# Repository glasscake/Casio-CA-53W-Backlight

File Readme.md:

# Casio-CA-53W Backlight Modification PCB

## Description
This is a PCB that adds backlight functonality to Casio-CA-53W style watches. It could potentially work with other Casio watches as well.

This project is still very green, a rev A board has been produced and is being tested. significant redesigns are still needed to improve preformance and relability in assembly.
Watch the project and see how development goes.

The design files are made in [KiCad](https://www.kicad.org/) an open source PCB design software.

## Make Your Own
Rev A boards have been produced from JLCPCB; uploading [Rev A.zip](Gerber%20Files/Rev%20A/Rev%20A.zip) to JLCPCB's or other PCB manufacturer's online portal and selecting flex PCB with ENIG sohuld get you boards similar to my own.  
Once a suitable design has been found more thorough ordering instructions will be provided. The current design also has a stiffener, this has no benifit and is not required.

Current limiting resistors can be ommited if diodes with a foward voltage close to 3.0v are carefuly chosen. I am using [Vishay VLMW15 serires](https://www.digikey.com/en/products/detail/vishay-semiconductor-opto-division/VLMW1500-GS08/3504672) 0402(imperial) LEDs at the moment.  
These LEDs have a typical forward voltage of 2.9 volts which means when using the Casio's 3.0v battery the foward current is around 5mA very well within the 20mA rating of the componets. So shunts or solder bridges may be used instead.  
0402 is the smallest componet the average enthusiast will be able to solder by hand so it was chosen for this project.  
the move to 0201(imperial) LEDs may come if 0402 componets are too large to fit and retain splash resistance in the watch.

## Copyright
Copyright 2025 NuE All rights reserved  
Private usage of this project by an individual with no intention to resell or distribute at profit the finished PCB, preassembled PCB, raw PCB, design files, or any item derived from this project is completly allowed.

At the moment this project is not open source. I am trying to figure out a license type that would allow contribution and private use but disallow an individual or company the ability to resell the componets, finished PCB, or design.

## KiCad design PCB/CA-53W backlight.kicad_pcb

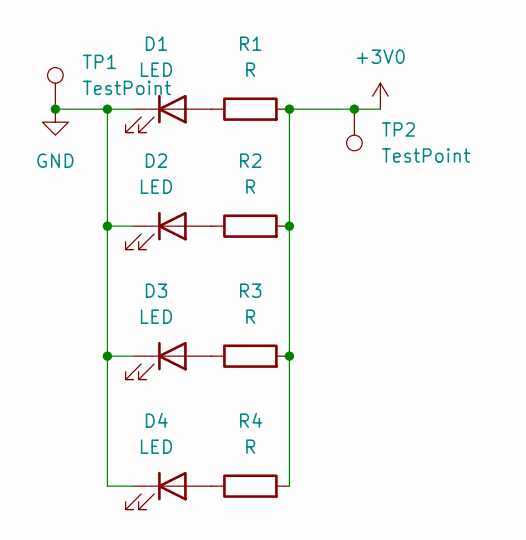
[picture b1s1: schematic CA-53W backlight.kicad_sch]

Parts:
D1, D2, D3, D4: LED; LED_0402_1005Metric
R1, R2, R3, R4: R; 402 jumper
TP1, TP2: TestPoint; TestPoint_Pad_D1.0mm

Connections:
+3V0: R1.2, R2.2, R3.2, R4.2, TP2.1
GND: D1.1 (K), D2.1 (K), D3.1 (K), D4.1 (K), TP1.1
unnamed: D1.2 (A), R1.1
unnamed: D2.2 (A), R2.1
unnamed: D3.2 (A), R3.1
unnamed: D4.2 (A), R4.1

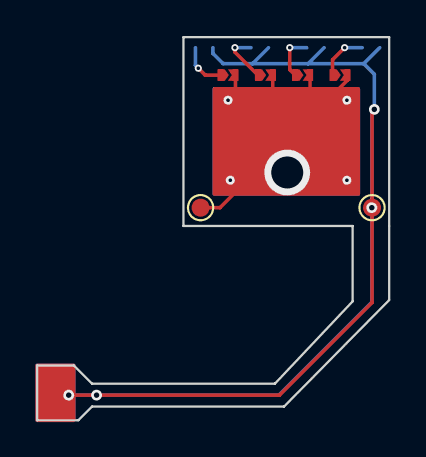
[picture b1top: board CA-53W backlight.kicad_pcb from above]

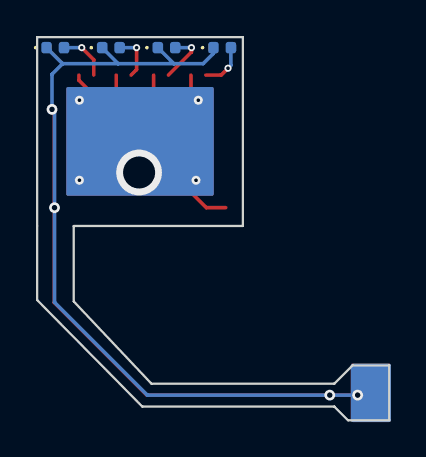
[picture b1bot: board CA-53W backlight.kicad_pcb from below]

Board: 2 copper layers, 19.6 x 21.3 mm, 10 parts (4 on the bottom side), 6 nets.

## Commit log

2025-01-17 Inital
    PCB Layout, basic components, pads and test points
2025-01-18 image and press button layout
    adding image for ref and starting to lay out press button
2025-01-18 Out for boards Rev A
    getting quoted through JLC PCB
2025-01-20 Cleanup and rename
    Cleaning up directories and renaming
2025-01-28 Readme testing
    readme
2025-01-28 readme updates
    updating readme
2025-01-28 gifs
    adding gifs
